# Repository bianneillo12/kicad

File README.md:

# Git Fundamentals Lab
Bianca Ianneillo

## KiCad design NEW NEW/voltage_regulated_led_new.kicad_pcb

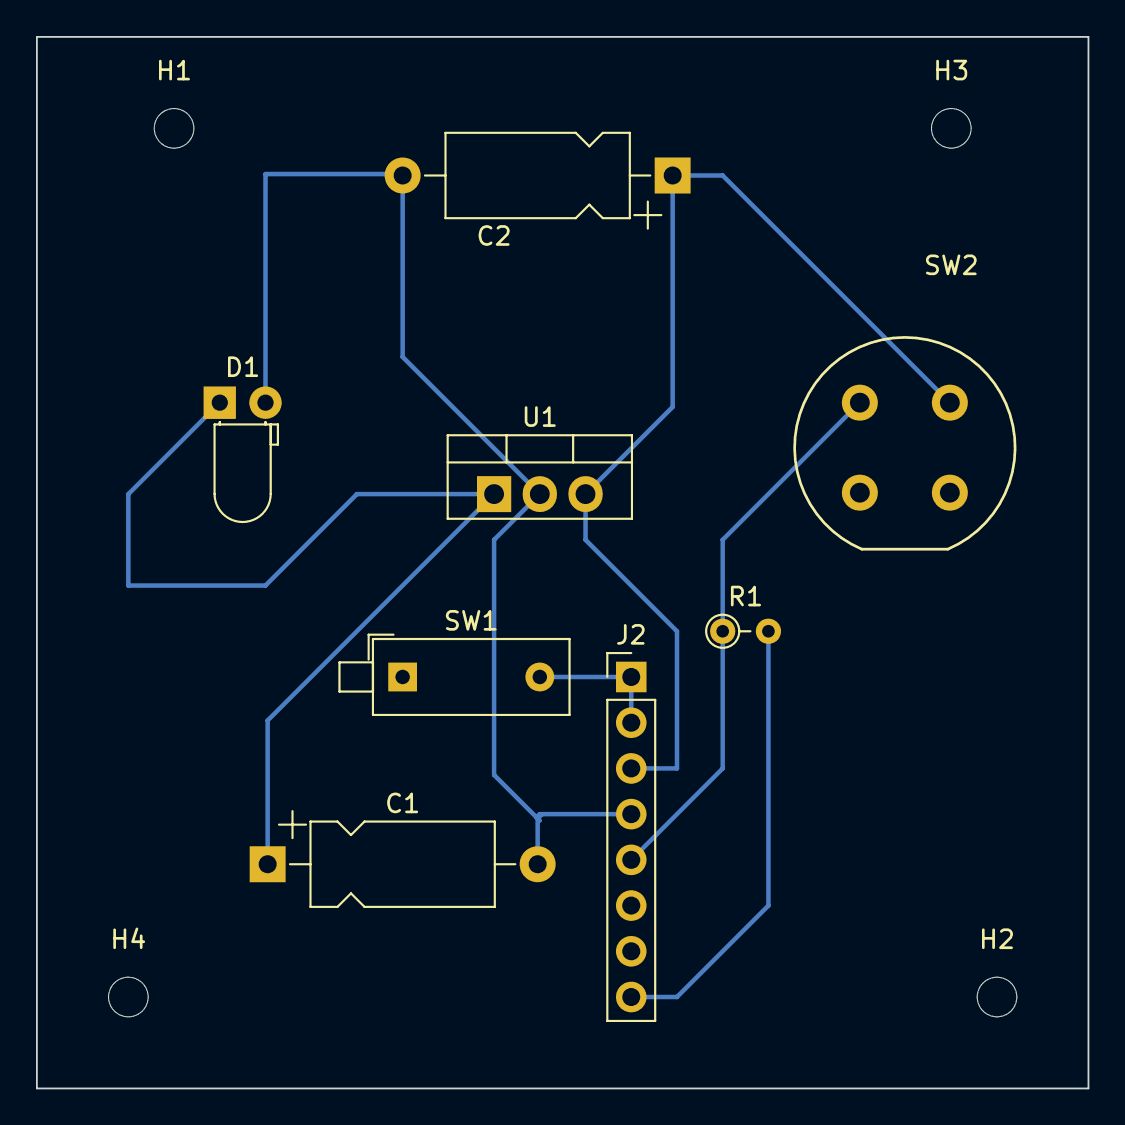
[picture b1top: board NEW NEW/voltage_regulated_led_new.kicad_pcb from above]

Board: 2 copper layers, 58.4 x 58.4 mm, 12 parts (0 on the bottom side), 5 nets.

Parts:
C1, C2: C_Polarized_US; CP_Axial_L10.0mm_D4.5mm_P15.00mm_Horizontal
D1: LED; LED_D3.0mm_Horizontal_O1.27mm_Z10.0mm
H1, H2, H3, H4: MountingHole; MountingHole_2.2mm_M2
J2: Conn_01x08_Pin; PinHeader_1x08_P2.54mm_Vertical
R1: R_US; R_Axial_DIN0204_L3.6mm_D1.6mm_P2.54mm_Vertical
SW1: SW_SPST; SW_DIP_SPSTx01_Piano_10.8x4.1mm_W7.62mm_P2.54mm
SW2: SW_Push; Push_E-Switch_KS01Q01
U1: LM7805_TO220; TO-220-3_Vertical

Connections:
+5V: C2.1, J2.3, SW2.2, U1.3 (VO)
/+9v: J2.1, J2.2, SW1.2 (B)
/Push-Button Activated LED/Vled: J2.8, R1.2
GND: C1.2, C2.2, D1.2 (A), J2.4, J2.5, J2.6, J2.7, R1.1, SW1.1 (A), SW2.1, U1.2 (GND)
unnamed: C1.1, D1.1 (K), U1.1 (VI)

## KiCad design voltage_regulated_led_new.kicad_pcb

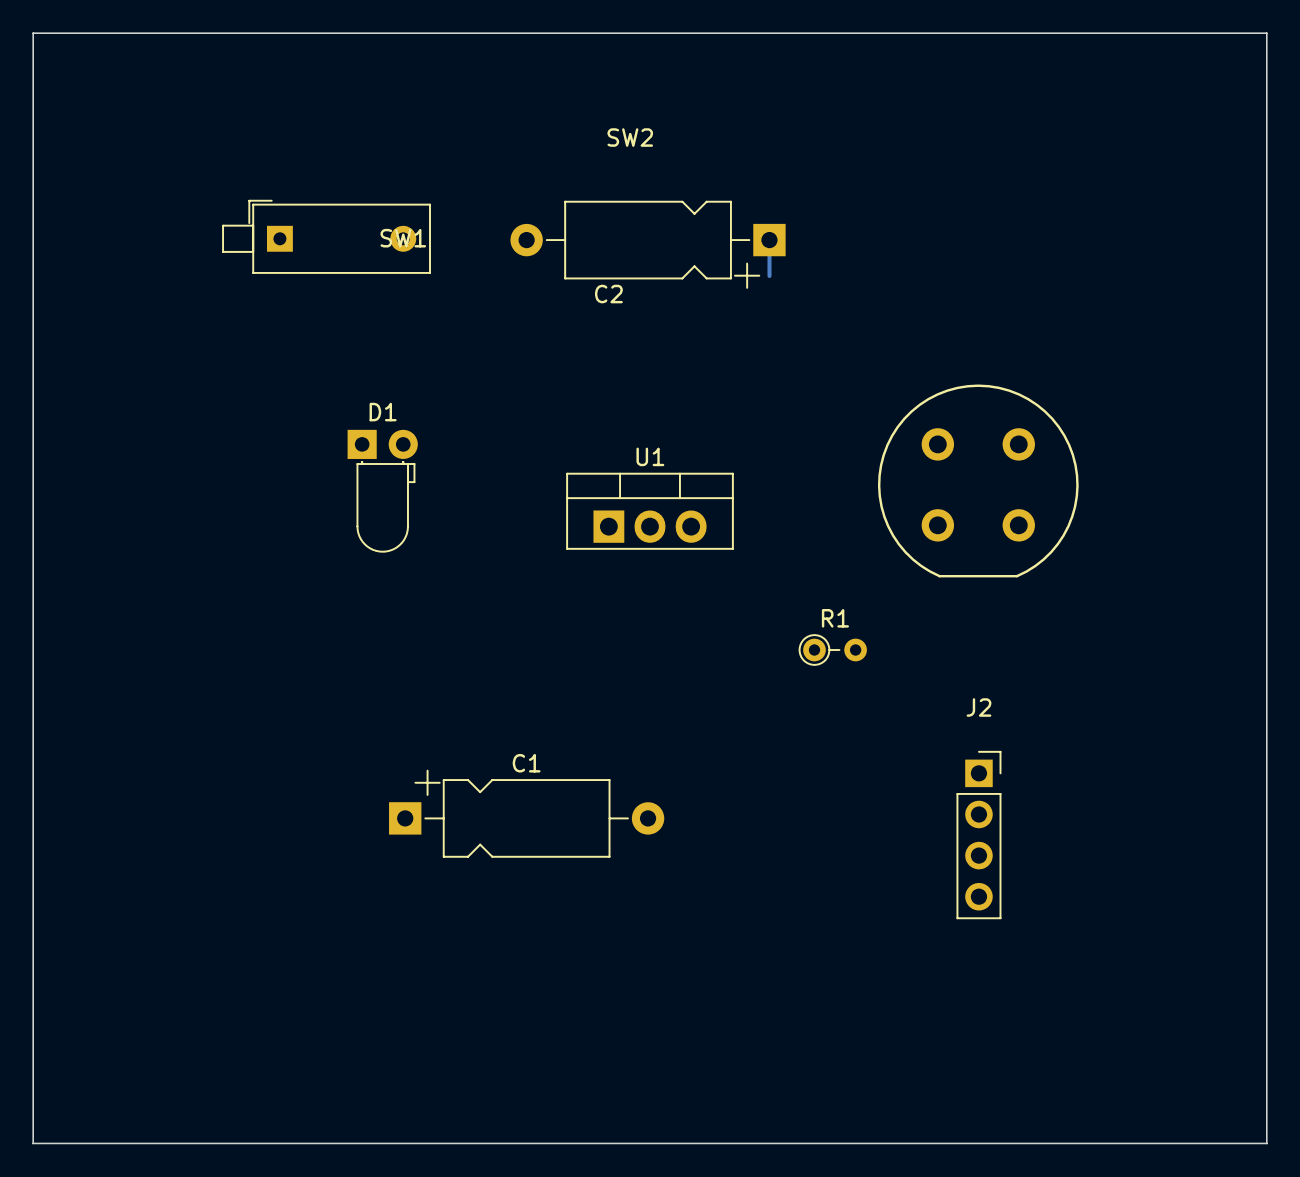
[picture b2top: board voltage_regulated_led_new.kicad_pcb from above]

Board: 2 copper layers, 76.2 x 68.6 mm, 8 parts (0 on the bottom side), 6 nets.

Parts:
C1, C2: C_Polarized_US; CP_Axial_L10.0mm_D4.5mm_P15.00mm_Horizontal
D1: LED; LED_D3.0mm_Horizontal_O1.27mm_Z10.0mm
J2: Conn_01x04_Pin; PinSocket_1x04_P2.54mm_Vertical
R1: R_US; R_Axial_DIN0204_L3.6mm_D1.6mm_P2.54mm_Vertical
SW1: SW_SPST; SW_DIP_SPSTx01_Piano_10.8x4.1mm_W7.62mm_P2.54mm
SW2: SW_Push; Push_E-Switch_KS01Q01
U1: LM7805_TO220; TO-220-3_Vertical

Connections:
+5V: C2.1, SW2.2, U1.3 (VO)
/Push-Button Activated LED/Vled: J2.1, R1.2
GND: C1.2, C2.2, J2.2, J2.3, U1.2 (GND)
unnamed: D1.2 (A), SW1.2 (B)
unnamed: C1.1, D1.1 (K), U1.1 (VI)
unnamed: R1.1, SW2.1

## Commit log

2023-10-06 add_files
2023-10-06 readme
2023-10-06 add files 2
2023-10-06 version update
2023-10-06 hail mary
2023-10-06 real edits this time!
